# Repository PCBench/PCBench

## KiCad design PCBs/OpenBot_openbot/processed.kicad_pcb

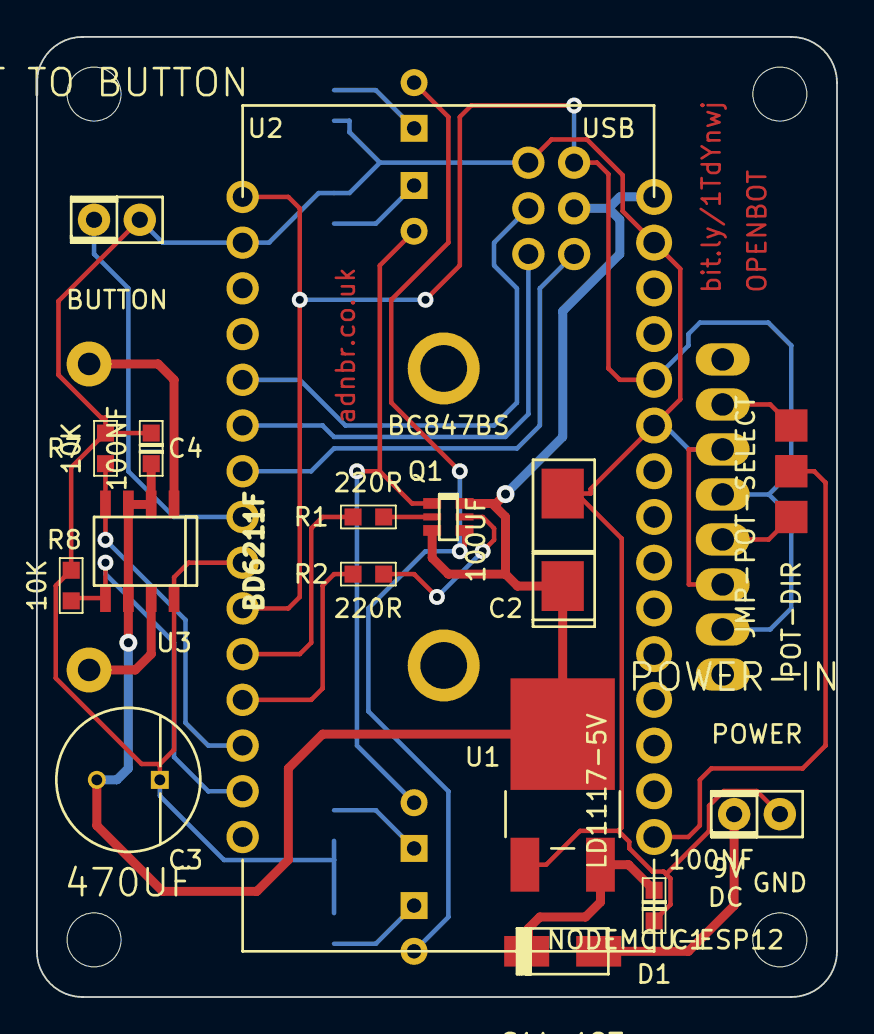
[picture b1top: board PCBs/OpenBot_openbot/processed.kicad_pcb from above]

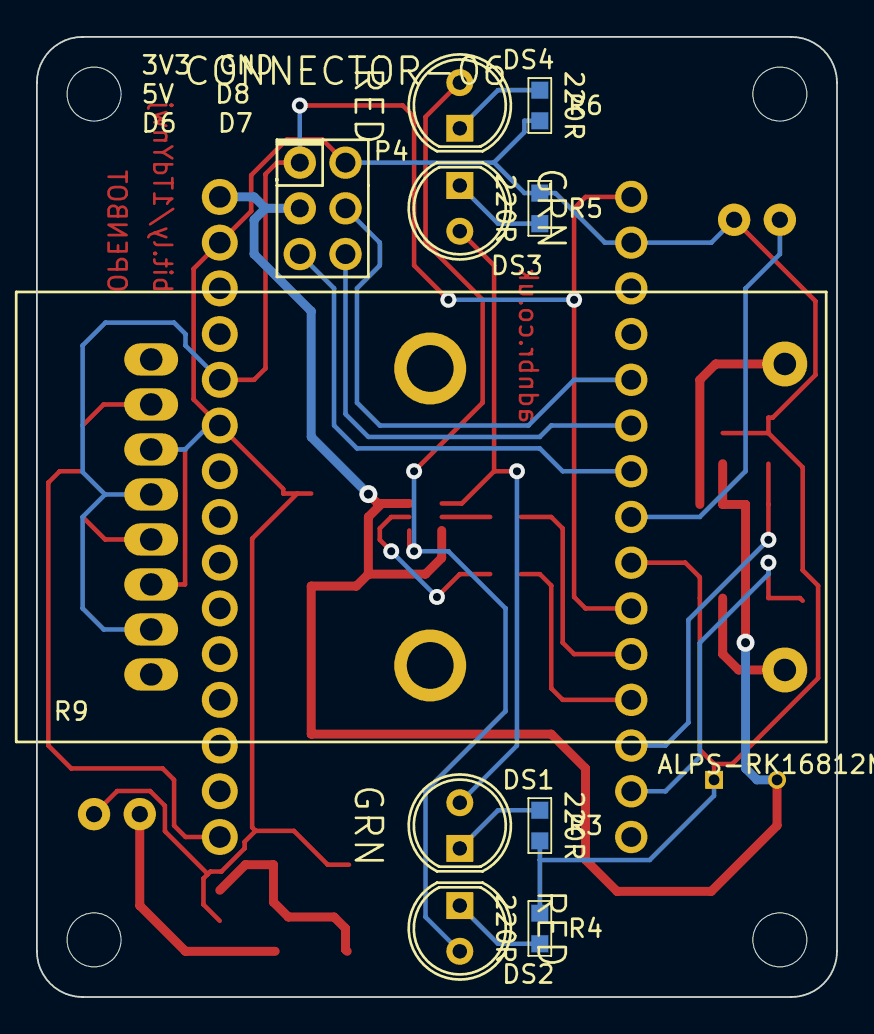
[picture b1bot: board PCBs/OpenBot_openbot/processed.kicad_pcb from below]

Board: 2 copper layers, 44.4 x 53.3 mm, 30 parts (10 on the bottom side), 26 nets.

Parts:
BUTTON: JST TO BUTTON; CONN-02
C1, C4: 100NF; CAPACITOR-NP-0603-REFLOW
C2: 100UF; CAP_POL_KEMET_C
C3: 470UF; CAPACITOR-POL-D_8MMxP_3.5MM
D1: S1A-127; DIODE-SMA
DS1, DS3: GRN; LED-5MM
DS2, DS4: RED; LED-5MM
M3-HOLE, M3-HOLE_2, M3-HOLE_3, M3-HOLE_4: VAL**; M3-HOLE
P4: CONNECTOR-06; CONN-06-2x3
POT-DIR: JMP-POT-SELECT; SJ-03
POWER: POWER-IN; CONN-02
Q1: BC847BS; SOT363
R1, R2, R3, R4, R5, R6: 220R; RESISTOR-0603-REFLOW
R7, R8: 10K; RESISTOR-0603-REFLOW
R9: ALPS-RK16812MG; ALPS-RK16812MG-10kBx2
U1: LD1117-5V; TO-252
U2: NODEMCU-ESP12; NODEMCU-DEVKIT
U3: BD6211F; SOP-8

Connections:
3V3: P4.1, R9.A1, R9.B3, U2.11, U2.16, U2.25
+5V: C2.A, C3.A, C4.2, P4.2, Q1.3, Q1.6, U1.2, U2.15, U3.2, U3.3, U3.6
/MOTOR-A: R9.MB, U3.1
/MOTOR-B: R9.MA, U3.7
GND: BUTTON.2, C1.1, C2.C, C3.C, C4.1, P4.6, POWER.2, R3.1, R4.1, R5.1, R6.1, R7.1, R8.1, R9.A3, R9.B1, U1.1, U2.10, U2.14, U2.17, U2.24, U3.8
LED-GREEN: R1.2, U2.26
LED-RED: R2.2, U2.27
MOTOR-FWD: R7.2, U2.28, U3.4
MOTOR-REV: R8.2, U2.29, U3.5
unnamed: POT-DIR.2, U2.1
unnamed: POT-DIR.3, R9.B2
unnamed: POT-DIR.1, R9.A2
unnamed: D1.A, POWER.1
unnamed: P4.3, U2.22
unnamed: P4.4, U2.21
unnamed: Q1.5, R2.1
unnamed: Q1.2, R1.1
unnamed: C1.2, D1.C, U1.3
unnamed: P4.5, U2.20
unnamed: DS2.C, R4.2
unnamed: DS4.C, R6.2
unnamed: DS1.A, DS3.A, Q1.1
unnamed: BUTTON.1, U2.23
unnamed: DS1.C, R3.2
unnamed: DS3.C, R5.2
unnamed: DS2.A, DS4.A, Q1.4

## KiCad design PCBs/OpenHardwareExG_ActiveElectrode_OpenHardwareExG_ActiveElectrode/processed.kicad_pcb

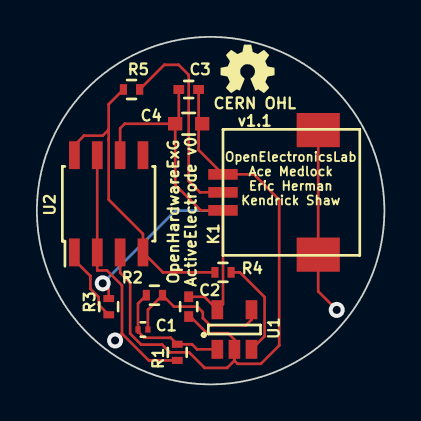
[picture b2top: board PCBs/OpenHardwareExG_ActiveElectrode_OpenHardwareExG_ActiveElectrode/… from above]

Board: 4 copper layers, 19.3 x 19.3 mm, 13 parts (1 on the bottom side), 10 nets.

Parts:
C1: 1nF; C_0201
C2, C3: 1uF; C_0402
C4: 10uF; C_0603
K1: CONN_3; DF50A-3P-1H
P1: CONN_1; electrode_pad
R1, R3, R5: 100; R_0402
R2, R4: 10k; R_0402
U1: LMP7715; SOT-23-5
U2: LMP7721; SOIC-8_3.9x4.9mm_Pitch1.27mm

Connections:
+5V: C2.1, C3.1, C4.1, K1.1, U1.5, U2.6
/BUFFERED_INPUT: R4.2, R5.1, U2.4, U2.8
/ELECTRODE: P1.1, R3.1
/GUARD_RING: R1.2, U2.2, U2.7
/GUARD_RING_DRIVER: C1.1, R1.1, R2.1, U1.1
/GUARD_RING_FILTERED_FEEDBACK: C1.2, R2.2, U1.4
/GUARD_RING_INPUT: R4.1, U1.3
/LINE_OUT: K1.2, R5.2
/PROTECTED_ELECTRODE: R3.2, U2.1
GND: C2.2, C3.2, C4.2, K1.3, U1.2, U2.3

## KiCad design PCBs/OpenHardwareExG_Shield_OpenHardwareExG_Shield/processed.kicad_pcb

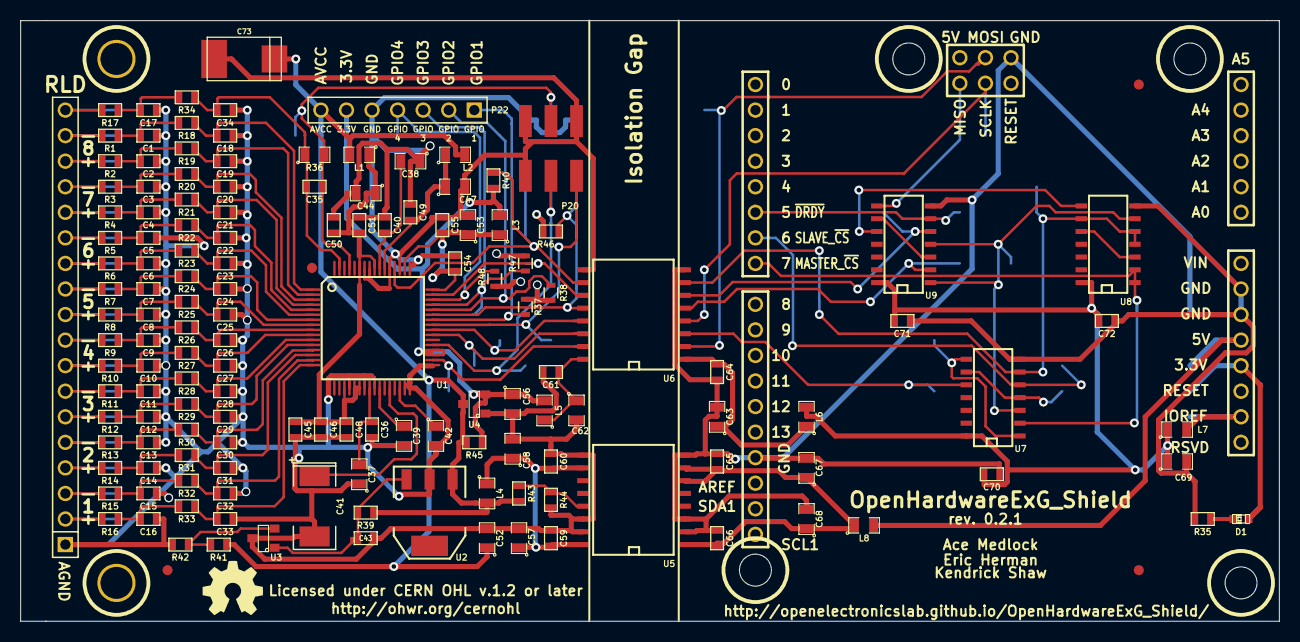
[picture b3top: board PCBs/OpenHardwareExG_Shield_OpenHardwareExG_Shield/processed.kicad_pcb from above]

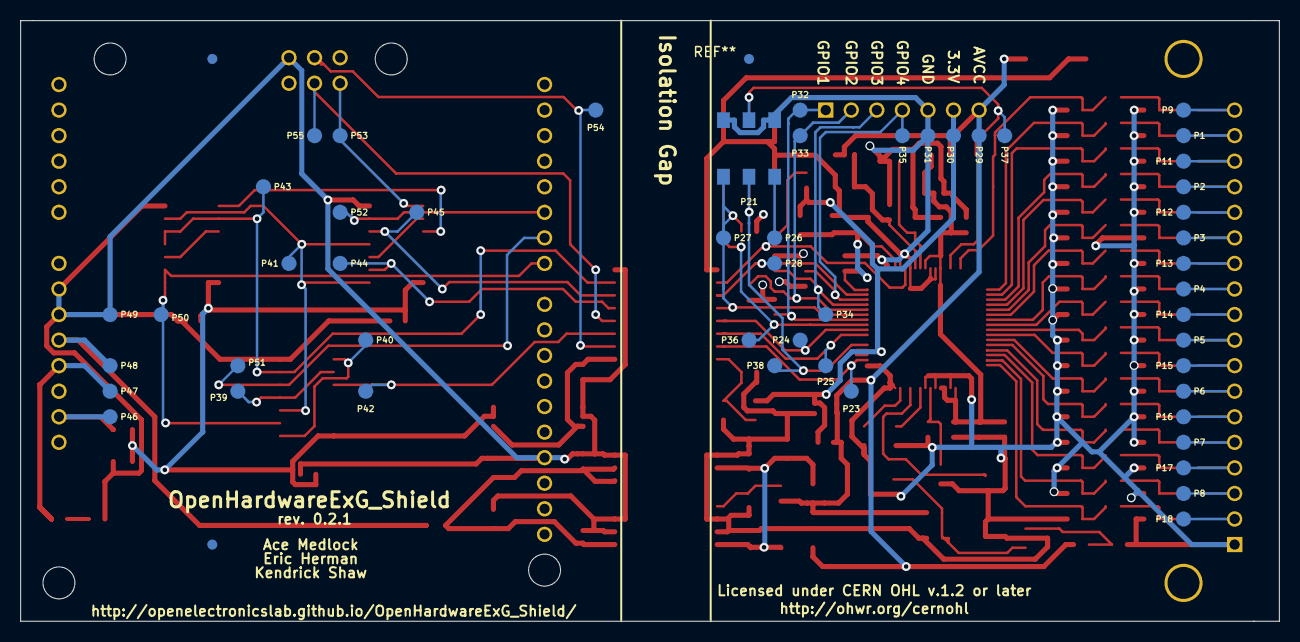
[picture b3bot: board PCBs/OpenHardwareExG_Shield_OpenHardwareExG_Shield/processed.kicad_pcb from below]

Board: 4 copper layers, 125.1 x 59.7 mm, 196 parts (51 on the bottom side), 104 nets.

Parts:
C1, C2, C3, C4, C5, C6, C7, C8, C9, C10, C11, C12, C13, C14, C15, C16, C17, C18, C19, C20, C21, C22, C23, C24, C25, C26, C27, C28, C29, C30, C31, C32, C33, C34: 270pF; SM0603
C35: 1.5nF; SM0603
C36, C40, C43, C45, C46, C48, C49, C50, C51, C54, C55, C59, C60, C61, C64, C65, C66, C70, C71, C72: 100nF; SM0603
C37, C38, C39, C42, C44, C47, C52, C53, C56, C57, C58, C62, C63, C67, C68, C69: 10uF; SM0805
C41: 100uF; SM2512
C73: 330uF; c_tant_D
D1: LED; LED-0603
Hole_M3, Hole_M3_2: VAL**; Hole_M3
L1, L2, L3, L4, L5, L6, L7, L8: MH2029-221Y; SM0805
P1, P2, P3, P4, P5, P6, P7, P8, P9, P11, P12, P13, P14, P15, P16, P17, P18, P23, P24, P25, P26, P27, P28, P29, P30, P31, P32, P33, P34, P35, P36, P37, P38, P39, P40, P41, P42, P43, P44, P45, P46, P47, P48, P49, P50, P51, P52, P53, P54, P55: CONN_1; POGO_PAD
P10: CONN_18; PIN_ARRAY_18x1
P19: ARDUINO_SHIELD; arduino_shield_with_holes
P20: CONN_3X2; 54202-G0803ALF
P21: CONN_3X2; 89898-303LF
P22: CONN_7; PIN_ARRAY_7x1
R1, R2, R3, R4, R5, R6, R7, R8, R9, R10, R11, R12, R13, R14, R15, R16, R17, R18, R19, R20, R21, R22, R23, R24, R25, R26, R27, R28, R29, R30, R31, R32, R33, R34: 2.61k; SM0603
R35: 560; SM0603
R36: 1M; SM0805
R37, R38, R47, R48: 10k; R_0603
R39: 68; SM0603
R40, R46: 10k; SM0603
R41: 10.0k; SM0603
R42: 8.45k; SM0603
R43: 0; SM0603
R44, R45: NI; SM0603
U1: ADS1299; TQFP_64
U2: Z0109MNT1G; SOT223
U3: TL431BIDBZR; SOT23
U4: 873-AAT3220IGY-33T1; SOT23
U5: ADUM6000; SO16W
U6: SI8663; SO16W
U7: 74LS02; SO14E
U8: 74LS00; SO14E
U9: 74LS125; SO14E

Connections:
+3.3V: D1.1, P19.93, P47.1
+3.3VADC: C53.1, C54.1, C55.1, L3.1, U1.48, U1.50
+5V: L8.2, P19.94, P48.1
/3.3V_ISO: C56.1, L3.2, L5.2, P22.6, P30.1, R40.1, R45.2, R46.1, U1.35, U1.36, U4.2
/ADS129x_CLK_ISO: P20.4, P21.4, P38.1, U1.37
/ADS129x_DAISY_IN_ISO: P20.2, P36.1, U1.41
/ADS129x_DOUT: P44.1, U6.5, U9.2
/ADS129x_DOUT_ISO: P21.6, P27.1, R46.2, U1.43, U6.12
/ADS129x_GPIO1_ISO: P22.1, P32.1, R37.1, U1.42
/ADS129x_GPIO2_ISO: P22.2, P33.1, R38.1, U1.44
/ADS129x_GPIO3_ISO: P22.3, P34.1, R47.1, U1.45
/ADS129x_GPIO4_ISO: P22.4, P35.1, R48.1, U1.46
/ADS129x_MOSI_ISO: P23.1, U1.34, U6.15
/ADS129x_SCLK_ISO: P24.1, U1.40, U6.13
/ADS129x_~CS~: P42.1, U6.3, U7.10
/ADS129x_~CS~_ISO: P25.1, U1.39, U6.14
/ADS129x_~DRDY~: P45.1, U6.6, U9.5
/ADS129x_~DRDY~_ISO: P28.1, U1.47, U6.11
/ARDUINO_VCC: L7.2, P19.91, P46.1
/AVDD: C44.1, C45.1, C46.1, C48.1, C50.1, C51.1, L1.1, U1.19, U1.21, U1.22, U1.56, U1.59
/AVDD1: C47.1, C49.1, L2.1, U1.54
/BIASINV: C35.2, P20.3, P21.3, P37.1, R36.2, U1.61
/BIASOUT: C34.1, C35.1, R34.2, R36.1, U1.63
/BIASOUT_FILT: P9.1, P10.18, R17.1
/IN1N: P8.1, P10.3, R15.1
/IN1P: P10.2, P18.1, R16.1
/IN2N: P7.1, P10.5, R13.1
/IN2P: P10.4, P17.1, R14.1
/IN3N: P6.1, P10.7, R11.1
/IN3P: P10.6, P16.1, R12.1
/IN4N: P5.1, P10.9, R9.1
/IN4P: P10.8, P15.1, R10.1
/IN5N: P4.1, P10.11, R7.1
/IN5P: P10.10, P14.1, R8.1
/IN6N: P3.1, P10.13, R5.1
/IN6P: P10.12, P13.1, R6.1
/IN7N: P2.1, P10.15, R3.1
/IN7P: P10.14, P12.1, R4.1
/IN8N: P1.1, P10.17, R1.1
/IN8P: P10.16, P11.1, R2.1
/MASTER: P43.1, U6.7, U7.6, U8.4, U8.5, U8.9
/MASTER_AND_MASTER_CS: P40.1, U7.1, U7.8
/MASTER_DOUT: U9.3, U9.9
/MASTER_ISO: P21.2, P26.1, R40.2, U1.52, U6.10
/MASTER_~CS~: P19.7, P50.1, U7.2, U8.1, U8.2
/MASTER_~DRDY~: P19.5, P52.1, U9.6
/MISO: P19.74, P53.1, U9.8
/MOSI: P19.75, P54.1, U6.2
/SCLK: P19.76, P55.1, U6.4
/SLAVE_AND_SLAVE_CS: P39.1, U7.4, U7.9
/SLAVE_~CS~: P19.6, P51.1, U7.5
/VIN_ISO: C52.1, C73.1, L1.2, L2.2, L4.2, P22.7, P29.1, R39.1, R41.1, R43.1, R45.1, U2.1, U4.3
/VSEL: R43.2, R44.2, U5.13
/~ENABLED_MISO~: U8.8, U9.10
/~MASTER~: P41.1, U7.3, U8.6, U9.1, U9.4
AGND: C1.2, C2.2, C3.2, C4.2, C5.2, C6.2, C7.2, C8.2, C9.2, C10.2, C11.2, C12.2, C13.2, C14.2, C15.2, C16.2, C17.2, C18.2, C19.2, C20.2, C21.2, C22.2, C23.2, C24.2, C25.2, C26.2, C27.2, C28.2, C29.2, C30.2, C31.2, C32.2, C33.2, C34.2, C36.1, C37.1, C38.1, C39.2, C40.1, C41.2, C42.2, C43.2, C44.2, C45.2, C46.2, C47.2, C48.2, C49.2, C50.2, C51.2, C52.2, C53.2, C54.2, C55.2, C56.2, C57.2, C58.2, C59.2, C60.2, C61.2, C62.2, C73.2, P10.1, P20.1, P20.5, P20.6, P21.1, P21.5, P22.5, P31.1, R37.2, R38.2, R42.2, R44.1, R47.2, R48.2, U1.20, U1.23, U1.25, U1.31, U1.32, U1.33, U1.49, U1.51, U1.53, U1.57, U1.58, U2.2, U3.3, U4.1, U5.9, U5.14, U5.15, U6.9
GND: C63.2, C64.2, C65.2, C66.2, C67.2, C68.2, C69.2, C70.2, C71.2, C72.2, P19.87, P19.95, P19.96, P19.99, P49.1, R35.2, U5.2, U5.3, U5.8, U6.8, U7.7, U8.7, U9.7
unnamed: C1.1, R1.2, R18.1
unnamed: C2.1, R2.2, R19.1
unnamed: C3.1, R3.2, R20.1
unnamed: C4.1, R4.2, R21.1
unnamed: C5.1, R5.2, R22.1
unnamed: C6.1, R6.2, R23.1
unnamed: C7.1, R7.2, R24.1
unnamed: C8.1, R8.2, R25.1
unnamed: C9.1, R9.2, R26.1
unnamed: C10.1, R10.2, R27.1
unnamed: C11.1, R11.2, R28.1
unnamed: C12.1, R12.2, R29.1
unnamed: C13.1, R13.2, R30.1
unnamed: C14.1, R14.2, R31.1
unnamed: C15.1, R15.2, R32.1
unnamed: C16.1, R16.2, R33.1
unnamed: C17.1, R17.2, R34.1
unnamed: C18.1, R18.2, U1.1
unnamed: C19.1, R19.2, U1.2
unnamed: C20.1, R20.2, U1.3
unnamed: C21.1, R21.2, U1.4
unnamed: C22.1, R22.2, U1.5
unnamed: C23.1, R23.2, U1.6
unnamed: C24.1, R24.2, U1.7
unnamed: C25.1, R25.2, U1.8
unnamed: C26.1, R26.2, U1.9
unnamed: C27.1, R27.2, U1.10
unnamed: C28.1, R28.2, U1.11
unnamed: C29.1, R29.2, U1.12
unnamed: C30.1, R30.2, U1.13
unnamed: C31.1, R31.2, U1.14
unnamed: C32.1, R32.2, U1.15
unnamed: C33.1, R33.2, U1.16
unnamed: C36.2, C37.2, U1.24
unnamed: C38.2, C40.2, U1.55
unnamed: C39.1, U1.26
unnamed: C41.1, U1.28
unnamed: C42.1, U1.30
unnamed: C43.1, R39.2, U2.3, U3.1
unnamed: C57.1, C58.1, C59.1, C60.1, L4.1, U5.10, U5.16
unnamed: C61.1, C62.1, L5.1, U6.16
unnamed: C63.1, C64.1, L6.1, U6.1
unnamed: C65.1, C66.1, C67.1, C68.1, L8.1, U5.1, U5.6, U5.7
unnamed: D1.2, R35.1
unnamed: R41.2, R42.1, U3.2
unnamed: U8.3, U8.10
VCC: C69.1, C70.1, C71.1, C72.1, L6.2, L7.1, U7.14, U8.14, U9.14

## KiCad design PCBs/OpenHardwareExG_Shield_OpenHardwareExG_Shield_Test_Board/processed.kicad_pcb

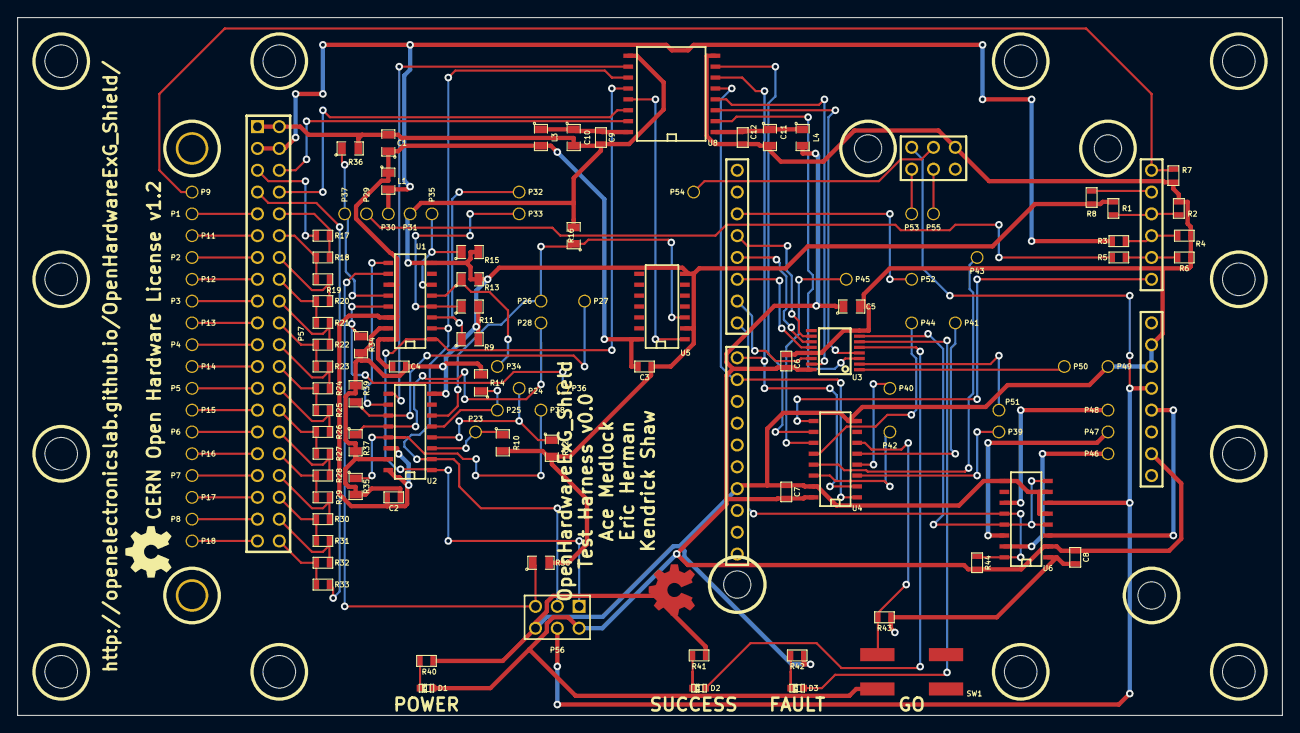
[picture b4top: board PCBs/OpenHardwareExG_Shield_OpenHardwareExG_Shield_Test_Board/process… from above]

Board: 4 copper layers, 147.3 x 81.3 mm, 137 parts (0 on the bottom side), 105 nets.

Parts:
C1, C5, C10, C11: 10uF; SM0805
C2, C3, C4, C6, C7, C8, C9, C12: 100nF; SM0603
D1, D2, D3: LED; LED-0603
Hole_M3, Hole_M3_2, Hole_M3_3, Hole_M3_4, Hole_M3_5, Hole_M3_6, Hole_M3_7, Hole_M3_8, Hole_M3_9, Hole_M3_10, Hole_M3_11, Hole_M3_12, Hole_M3_13, Hole_M3_14: VAL**; Hole_M3
L1, L3, L4: MH2029-221Y; SM0805
P1, P2, P3, P4, P5, P6, P7, P8, P9, P11, P12, P13, P14, P15, P16, P17, P18, P23, P24, P25, P26, P27, P28, P29, P30, P31, P32, P33, P34, P35, P36, P37, P38, P39, P40, P41, P42, P43, P44, P45, P46, P47, P48, P49, P50, P51, P52, P53, P54, P55: CONN_1; POGO_PIN_BASE
P19: ARDUINO_SHIELD; arduino_shield_with_holes
P56: CONN_3X2; pin_array_3x2
P57: CONN_20X2; PIN_ARRAY_20X2
R1, R3, R5, R43, R44: 10k; SM0603
R2, R4, R6: 1k; SM0603
R7: 5.1K; SM0603
R8, R18, R19, R20, R21, R22, R23, R24, R25, R26, R27, R28, R29, R30, R31, R32: 100; SM0603
R9, R10, R11, R12, R13, R14, R15, R16, R34, R35, R36, R37, R38, R39: 1M; SM0805
R17, R33: 15k; SM0603
R40, R41, R42: 560; SM0603
SW1: SW_PUSH; smt-tactile-button
U1, U2, U4: 74HC165; SO16E
U3: 74HC595PWR; TSSOP16
U5: 74LS125; SO14E
U6: TPS2095D; SO16E
U8: SI8661; SO16W

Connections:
+3.3V: P19.93, U6.3
+5V: P19.88, P19.94, P56.4, U6.6
/3.3V_BOGUS_ISO: L1.2, P30.1, P57.3, P57.4, R3.1
/3.3V_BOGUS_ISO_DATA: C9.1, C10.1, L3.1, U8.16
/A1: P19.55, R5.2, R6.1
/A2: P19.56, R3.2, R4.1
/A3: P19.57, R1.2, R2.1
/A4: P19.58, R8.2
/ADS129x_CLK_BOGUS_ISO: P38.1, R35.1, U2.13
/ADS129x_DAISY_IN_BOGUS_ISO: P36.1, R34.1, U1.13
/ADS129x_DOUT: P44.1, U4.12
/ADS129x_DOUT_BOGUS_ISO: P27.1, R39.1, U2.11
/ADS129x_GPIO1_BOGUS_ISO: P32.1, R9.1, U1.3
/ADS129x_GPIO2_BOGUS_ISO: P33.1, R11.1, U1.4
/ADS129x_GPIO3_BOGUS_ISO: P34.1, R13.1, U1.5
/ADS129x_GPIO4_BOGUS_ISO: P35.1, R15.1, U1.6
/ADS129x_MOSI_BOGUS_ISO: P23.1, R10.1, U2.3
/ADS129x_SCLK_BOGUS_ISO: P24.1, R12.1, U2.4
/ADS129x_~CS~: P42.1, U4.14
/ADS129x_~CS~_BOGUS_ISO: P25.1, R14.1, U2.5
/ADS129x_~DRDY~: P45.1, U4.11
/ADS129x_~DRDY~_BOGUS_ISO: P28.1, R37.1, U2.12
/ARDUINO_VCC: C5.1, C6.1, C7.1, C8.1, D1.1, L4.2, P19.91, P56.2, R44.2, SW1.2, U3.16, U4.16, U6.2
/BIASINV: P37.1, R36.1, U1.12
/BIASOUT_FILT: P9.1, P19.59, R7.1
/ENABLE_SHIELD: U3.7, U6.4, U6.8, U6.13
/FAULT_LED: D3.1, U3.6
/GO_BUTTON: R43.1, SW1.1, U4.6
/IN1N: P8.1, P57.37
/IN1N_LADDER: P57.38, R31.2, R32.2
/IN1P: P18.1, P57.39
/IN1P_LADDER: P57.40, R32.1, R33.1
/IN2N: P7.1, P57.33
/IN2N_LADDER: P57.34, R29.2, R30.2
/IN2P: P17.1, P57.35
/IN2P_LADDER: P57.36, R30.1, R31.1
/IN3N: P6.1, P57.29
/IN3N_LADDER: P57.30, R27.2, R28.2
/IN3P: P16.1, P57.31
/IN3P_LADDER: P57.32, R28.1, R29.1
/IN4N: P5.1, P57.25
/IN4N_LADDER: P57.26, R25.2, R26.2
/IN4P: P15.1, P57.27
/IN4P_LADDER: P57.28, R26.1, R27.1
/IN5N: P4.1, P57.21
/IN5N_LADDER: P57.22, R23.2, R24.2
/IN5P: P14.1, P57.23
/IN5P_LADDER: P57.24, R24.1, R25.1
/IN6N: P3.1, P57.17
/IN6N_LADDER: P57.18, R21.2, R22.2
/IN6P: P13.1, P57.19
/IN6P_LADDER: P57.20, R22.1, R23.1
/IN7N: P2.1, P57.13
/IN7N_LADDER: P57.14, R19.2, R20.2
/IN7P: P12.1, P57.15
/IN7P_LADDER: P57.16, R20.1, R21.1
/IN8N: P1.1, P57.9
/IN8N_LADDER: P57.10, R17.2, R18.2
/IN8P: P11.1, P57.11
/IN8P_LADDER: P57.12, R18.1, R19.1
/LED1: D1.2, R40.1
/LED2: D2.2, R41.1
/LED3: D3.2, R42.1
/MASTER: P43.1, U4.13
/MASTER_AND_MASTER_CS: P40.1, U4.4
/MASTER_BOGUS_ISO: P26.1, R16.1, U2.6, U5.3
/MASTER_~CS~: P50.1, U3.1
/MASTER_~DRDY~: P19.2, P52.1
/MIDDLE_CARRY: U1.9, U2.10
/MISO: P19.74, P53.1
/MOSI: P19.75, P54.1
/SCLK: P19.76, P55.1
/SHIELD_3.3V: P47.1, U6.14
/SHIELD_5V: P48.1, U6.11
/SHIELD_VCC: P46.1, U6.15
/SHIFT_CARRY: U4.10, U8.7
/SHIFT_CARRY_BOGUS_ISO: U2.9, U8.10
/SHIFT_CLK: P19.8, U4.2, U8.6
/SHIFT_CLK_BOGUS_ISO: P56.3, U1.2, U2.2, U8.11
/SHIFT_EXT_CARRY_BOGUS_ISO: P56.5, R38.1, U1.10
/SHIFT_IN: P19.54, U4.9
/SHIFT_OUT: P19.6, U3.14
/SHIFT_OUT_RCLK: P19.5, U3.12
/SHIFT_OUT_SRCLK: P19.4, U3.11
/SHIFT_OUT_~SRCLR~: P19.3, U3.10
/SHIFT_SH_~LD~: P19.9, U4.1, U8.5
/SHIFT_SH_~LD~_BOGUS_ISO: P56.1, U1.1, U2.1, U8.12
/SIGNAL_A: U3.3, U8.2
/SIGNAL_A_BOGUS_ISO: P57.6, U8.15
/SIGNAL_A_LADDER: P57.5, R17.1
/SIGNAL_B: U3.4, U8.3
/SIGNAL_B_BOGUS_ISO: P57.8, U8.14
/SIGNAL_B_LADDER: P57.7, R33.2
/SLAVE_AND_SLAVE_CS: P39.1, U4.3
/SLAVE_~CS~: P51.1, U3.2
/SUCCESS_LED: D2.1, U3.5
/VCC_DATA: C11.1, C12.1, L4.1, U8.1
/VIN_BOGUS_ISO: P29.1, R5.1
/~MASTER~: P41.1, U4.5
/~SEND_TO_GND~_MASTER: U3.15, U8.4
/~SEND_TO_GND~_MASTER_BOGUS_ISO: U5.1, U8.13
/~SHIELD_SHORTED~: P19.7, R44.1, U6.12, U6.16
GND: C1.2, C2.2, C3.2, C4.2, C9.2, C10.2, P31.1, P57.1, P57.2, R1.1, R8.1, R9.2, R10.2, R11.2, R12.2, R13.2, R14.2, R15.2, R16.2, R34.2, R35.2, R36.2, R37.2, R38.2, R39.2, U1.8, U1.15, U2.8, U2.15, U5.2, U5.7, U8.9
GNDPWR: C5.2, C6.2, C7.2, C8.2, C11.2, C12.2, P19.87, P19.95, P19.96, P19.99, P49.1, P56.6, R2.2, R4.2, R6.2, R7.2, R40.2, R41.2, R42.2, R43.2, U3.8, U3.13, U4.8, U4.15, U6.1, U6.5, U6.7, U6.9, U8.8
VCC: C1.1, C2.1, C3.1, C4.1, L1.1, L3.2, U1.11, U1.14, U1.16, U2.14, U2.16, U5.14

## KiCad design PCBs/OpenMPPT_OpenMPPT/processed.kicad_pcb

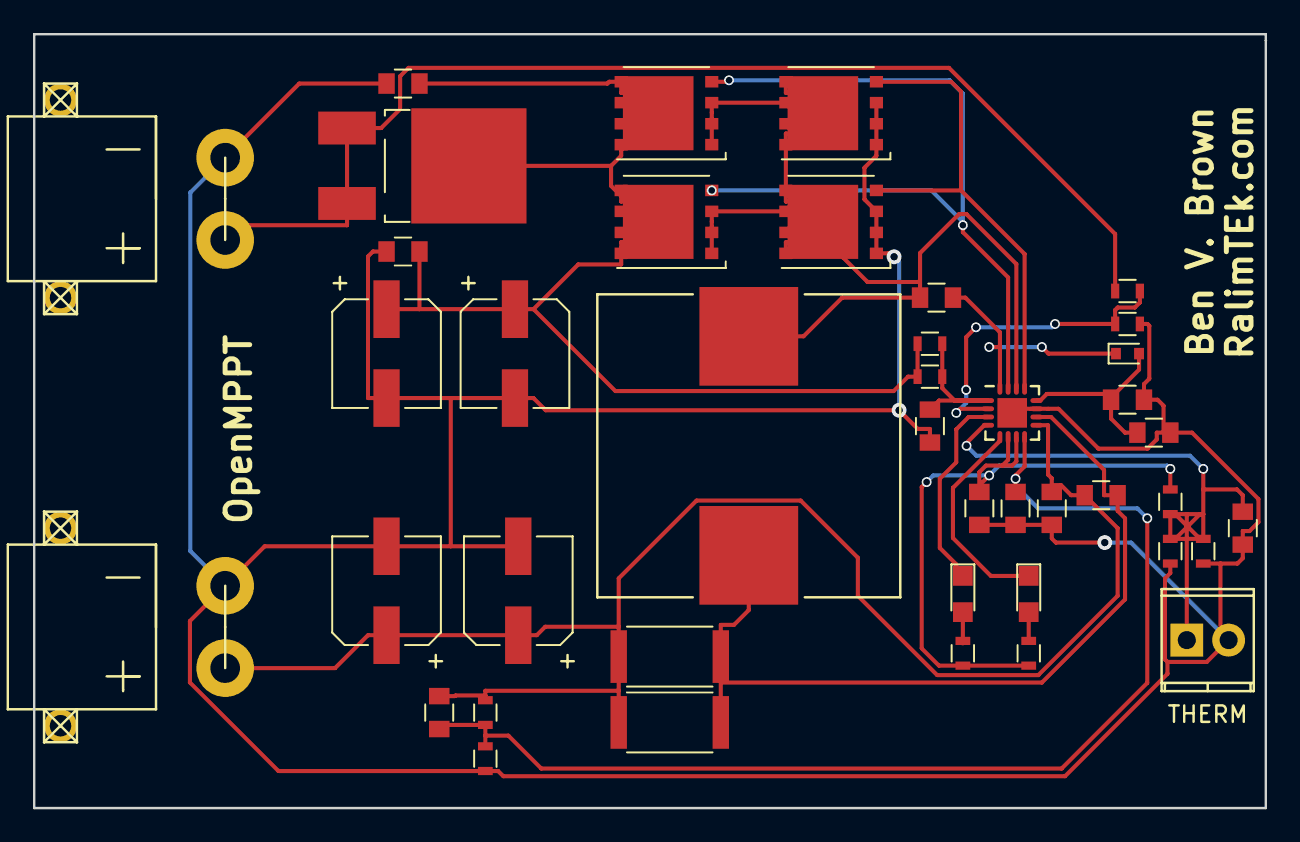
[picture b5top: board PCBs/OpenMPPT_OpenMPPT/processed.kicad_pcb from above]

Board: 2 copper layers, 74.8 x 47.0 mm, 42 parts (0 on the bottom side), 19 nets.

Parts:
C101: -; C_0805
C102, C103, C106, C107, C110, C115: 1.0uF; C_0805
C104, C105, C109, C112, C113: 0.1uF; C_0805
C108, C111, C114, C116: CP; CP_Elec_6.3x7.7
D101: MBRD10100CT; TO-252-2_Rectifier
D102: D_Schottky; D_SOD-523
D103, D104: LED; LED_0805
J101: THERM; TerminalBlock_Pheonix_MPT-2.54mm_2pol
J103, J104: XT60; XT30PW_Male
L101: 3.3uH; Inductor_Wurth_HCI-1890
Q101, Q102, Q103, Q104: FDMS8050; TDSON-8-1
R101: 10k; R_0603
R102, R108, R109: 5.23k; R_0603
R103: 30.1k; R_0603
R105: -; R_0603
R106: 10; R_0603
R110, R113: 0.01; R_2512
R111, R114: 499k; R_0603
R112: 100k; R_0603
R115: 36k; R_0603
U101: BQ24650; QFN-16-1EP_3x3mm_Pitch0.5mm

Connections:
/HIGH_DRIVE: Q101.4, Q103.4, U101.15
/LOW_DRIVE: Q102.4, Q104.4, U101.13
/MPPTSET: R114.2, R115.1, U101.2
/STAT1: D103.1, U101.3
/STAT2: D104.1, U101.5
/VREF: C103.1, R102.1, R108.1, R109.1, U101.6, U101.7
GND: C101.2, C102.1, C103.2, C104.2, C106.2, C107.2, C108.2, C110.2, C111.2, C113.1, C114.2, C115.2, C116.2, J101.2, J103.2, J104.2, Q102.1, Q102.2, Q102.3, Q104.1, Q104.2, Q104.3, R101.2, R103.2, R112.2, R115.2, U101.11, U101.17
unnamed: C101.1, J101.1, R101.1, R102.2, R103.1, U101.4
unnamed: C102.2, R105.2, R106.2, U101.1
unnamed: C104.1, C107.1, D102.2, U101.12
unnamed: C105.1, L101.1, Q101.1, Q101.2, Q101.3, Q102.5, Q103.1, Q103.2, Q103.3, Q104.5, U101.14
unnamed: C105.2, D102.1, U101.16
unnamed: C106.1, C108.1, C114.1, C115.1, D101.2, Q101.5, Q103.5, R105.1, R106.1
unnamed: C109.1, C110.1, C111.1, C112.2, C116.1, J104.1, R110.1, R111.1, R113.2, U101.9
unnamed: C109.2, L101.2, R110.2, R113.1, U101.10
unnamed: C112.1, C113.2, R111.2, R112.1, U101.8
unnamed: D101.1, D101.3, J103.1, R114.1
unnamed: D103.2, R108.2
unnamed: D104.2, R109.2

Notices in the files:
PCBs/OpenHardwareExG_ActiveElectrode_OpenHardwareExG_ActiveElectrode/processed.kicad_pcb:
CERN OHL
PCBs/OpenHardwareExG_Shield_OpenHardwareExG_Shield/processed.kicad_pcb:
Licensed under CERN OHL v.1.2 or later
PCBs/OpenHardwareExG_Shield_OpenHardwareExG_Shield_Test_Board/processed.kicad_pcb:
CERN Open Hardware License v1.2
